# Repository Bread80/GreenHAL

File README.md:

### Proposed Amstrad HAL/PAL Replacement

This is *prototype* design for a replacement for the HAL/PAL memory manager in an Amstrad CPC6128.
This project has *NOT* been tested.
The pinouts of these designs are different those of the original Amstrad HAL/PAL and some form of adapter will be required.

The design uses one of two chips from the Renesas GreenPAK range - https://www.renesas.com/eu/en/products/programmable-mixed-signal-asic-ip-products/greenpak-programmable-mixed-signal-products

The chips used are:
* SLG46826G - available in a TSSOP package
* SLG46826V - available in a QFN package
* SLG46826V-DIP - the same chip as above but in the PCB-DIP package

The design files are identical except for the package setting. Note that the pinouts are flipped between the TSSOP and QFN packages.

These chips where chosen because they can be (re)programmed via an I2C connection. This means a) they can be reprogrammed multiple times and b) they can be programmed without needing an expesive development board.

At this stage this project assumes the use of a programmer and extra software (and a microcontroller) will need to be written to enable I2C programming. However, the design files for doing so are included here.

Also included here is an adapter PCB to mount an SLG46826V-DIP IC into the original HAL socket.

Files included:
* *.gp6 - Design files for use with the Renesas Go Configure software which can be downloaded from https://www.renesas.com/eu/en/software-tool/go-configure-software-hub
* *_NVM.txt - Exports of the NVM data which will be needed to program the IC(s) via I2C. (See below)
* AmstradHALTests.txt - The results of tests run against an Amstrad HAL/PAL.
* GreenHALTests.txt - Results of the same tests run against the GreenHAL design.
* DIPDapter (folder) - The design for an adapter PCB between the -DIP variant of the chip and the Amstrad HAL socket.

## Chip Programming with a Dev Board
1) Open the appropriate .gp6 file with the Go COnfigure software
2) Insert the chip (and adapter if needed) into the Dev Board.
3) Plug the Dev Board into your computer (via USB).
4) In the Go Configure software click 'Debug' on the toolbar. The debugging Controls will appear on the right hand panel.
5) Click Change Platform and select your model of Dev Board.
6) Click the Program button/dropdown. This should now program your chip and give a confirmation message.

## Chip Programming via I2C (without a Dev Board)
As mentioned the necessary software etc for this has not been developed yet. If you want to try yourself these are the steps you'll need to go through:

For this you'll need a suitable microcontroller with I2C outputs.
You'll need to process the relevant NVM file from the repository into suitable I2C data.
For an unprogrammed chip: You'll need to encode the I2C device address on the appropriate pins (by connecting them to 5V or ground) to match the device address you're sending data to. (Consult the datasheet for the IC to ascertain which pins to use).
For an already programmed chip: the previous step is unecessary as the I2C address will now be programmed into the device. This address is set to 0001 (binary). You'll need to use this address programming software.
You'll need to connect the chips ground and power pins to power the device.
You'll need to connect the I2C pins (SDA and SCL) to the appropriate pins on your microcontroller.
You'll also need pullup resistors on these pins. 2.2k ohms *should* be suitable here.
And finally you can get the microcontroller to send the data to the IC. :phew:

The DIPDapter board included with the project includes a header for the SDA, SCL and ground pins.

## Chip Programming via I2C (with a Dev Board)
The Go Configure software can also program a chip via I2C using the Dev Board. This may be useful where a chip has been soldered in place.

To do this follow the steps under Chip Porgramming with a Dev Board except:
You will need to connect the power, ground, SDA and SCL pins of the chip to the external connector of the Dev Board. For a QFN chip the pinout here is the same as the chip. For a TSSOP chip the pin ordering is reversed!

Follow the notes under Chip Programming via I2C (without a dev board) with regards to configuring an I2C address for the chip. I.e. connect pins to 5v/ground as needed for an unprogrammed chip. For a previously programmed chip the on chip address will be used instead.

I the Debugging Controls of the Go Configure software find the Device setting and change from Onboard to the I2C device address. Either as configure on the pins (for an unprogrammed device) or '0001' for a previously programmed device.

© Mike Sutton, 2023
Licence: CERN-OHL-P-2.0

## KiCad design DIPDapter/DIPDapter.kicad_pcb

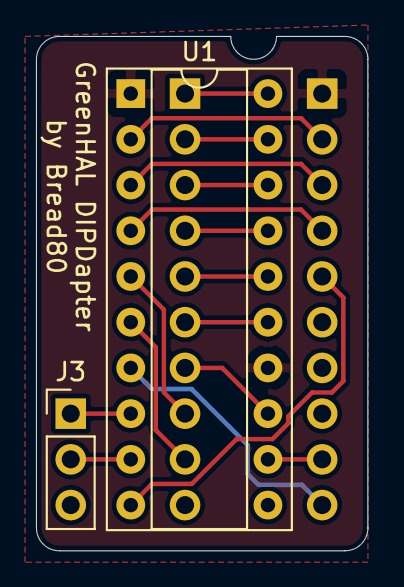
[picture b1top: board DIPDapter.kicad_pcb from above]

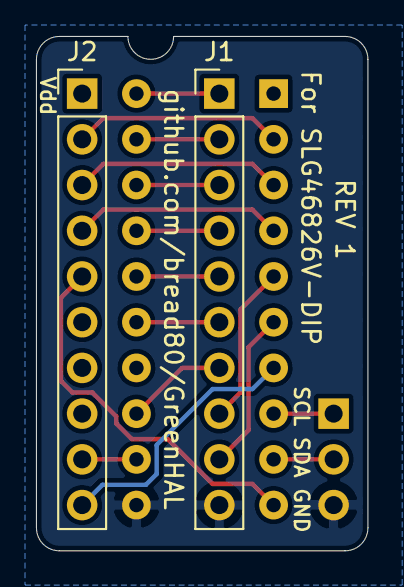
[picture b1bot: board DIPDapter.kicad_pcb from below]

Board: 2 copper layers, 18.4 x 28.6 mm, 4 parts (2 on the bottom side), 19 nets.

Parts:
J1, J2: Conn_01x10_Male; PinHeader_1x10_P2.54mm_Vertical
J3: Conn_01x03_Male; PinHeader_1x03_P2.54mm_Vertical
U1: SLG46826V-DIP; DIP-20_W7.62mm_Socket

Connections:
/A14: J1.9, U1.6
/A14OUT: J2.2, U1.2
/A15: J1.8, U1.5
/A15OUT: J2.9, U1.12
/D0: J1.2, U1.19
/D1: J1.5, U1.16
/D2: J1.6, U1.15
/RAMDIS: J1.4, U1.17
/SCL: J3.1, U1.8
/SDA: J3.2, U1.9
/SELECT: J1.1, U1.20
/~CAS: J1.7, U1.13
/~CAS0: J2.4, U1.4
/~CAS1: J2.5, U1.10
/~CPU: J2.10, U1.7
/~IOWR: J2.3, U1.3
/~RESET: J1.3, U1.18
GND: J1.10, J3.3, U1.11
VDD: J2.1, U1.1, U1.14
